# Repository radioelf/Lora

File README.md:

# Lora
Lora Radio
Molule E220 https://www.ebyte.com/en/product-view-news.html?id=1207

    Creative Commons License Disclaimer

  UNLESS OTHERWISE MUTUALLY AGREED TO BY THE PARTIES
  AND MAKES NO REPRESENTATIONS OR WARRANTIES OF ANY
  STATUTORY OR OTHERWISE, INCLUDING, WITHOUT LIMITAT
  FITNESS FOR A PARTICULAR PURPOSE, NONINFRINGEMENT,
  ACCURACY, OR THE PRESENCE OF ABSENCE OF ERRORS, WH
  DO NOT ALLOW THE EXCLUSION OF IMPLIED WARRANTIES,
  EXCEPT TO THE EXTENT REQUIRED BY APPLICABLE LAW, I
  ON ANY LEGAL THEORY FOR ANY SPECIAL, INCIDENTAL, C
  ARISING OUT OF THIS LICENSE OR THE USE OF THE WORK
  POSSIBILITY OF SUCH DAMAGES.

  http://creativecommons.org/licenses/by-sa/3.0/

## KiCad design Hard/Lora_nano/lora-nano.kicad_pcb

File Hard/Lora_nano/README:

PCB for Arduino Nano and module E220
Application: KiCad x86_64 on x86_64

Version: 7.0.0-rc1-unknown-00d77f624a~164~ubuntu22.04.1, release build

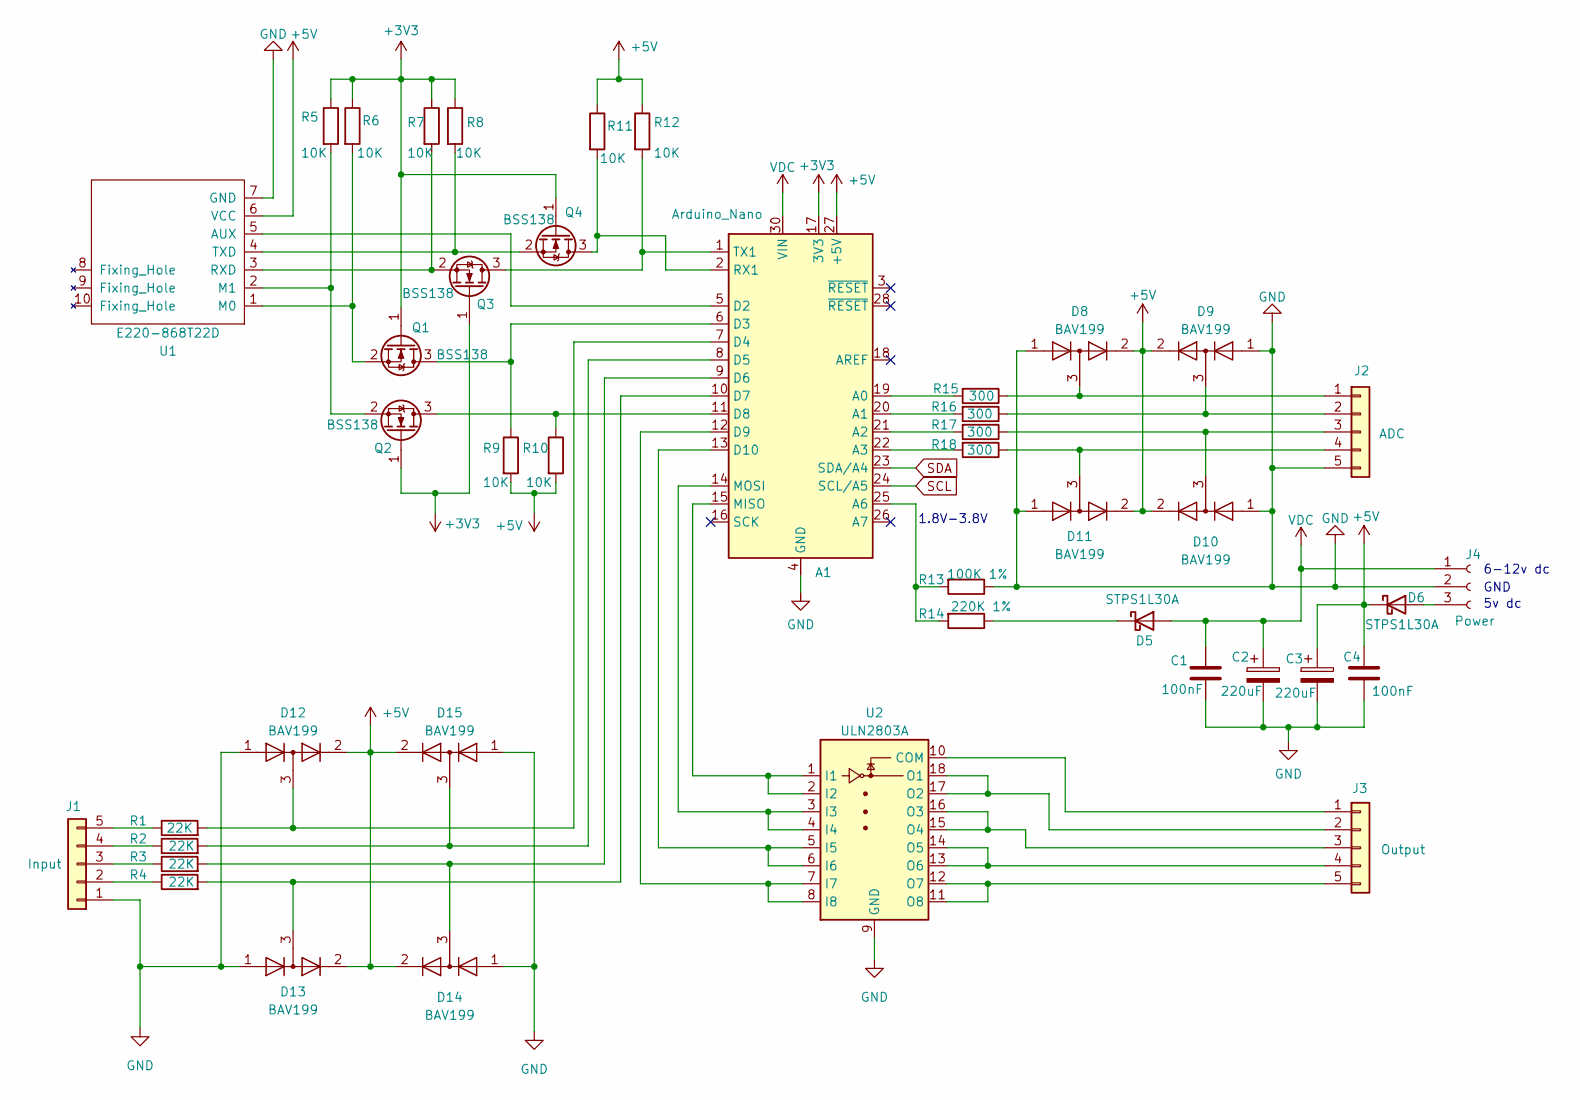
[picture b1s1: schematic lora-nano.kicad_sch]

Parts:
A1: Arduino_Nano
C1, C4: 100nF; C_0805_2012Metric
C2: 220uF; CP_Elec_8x6.2
C3: 220uF; CP_Elec_5x5.9
D5, D6: STPS1L30A; D_2010_5025Metric_Pad1.52x2.65mm_HandSolder
D8, D9, D10, D11, D12, D13, D14, D15: BAV199; SOT-23
J1: Input; PhoenixContact_MCV_1,5_5-G-3.5_1x05_P3.50mm_Vertical
J2: ADC; PhoenixContact_MCV_1,5_5-G-3.5_1x05_P3.50mm_Vertical
J3: Output; PhoenixContact_MCV_1,5_5-G-3.5_1x05_P3.50mm_Vertical
J4: Power; PhoenixContact_MCV_1,5_3-G-5.08_1x03_P5.08mm_Vertical
Q1, Q2, Q3, Q4: BSS138; SOT-23
R1, R2, R3, R4: 22K; R_0805_2012Metric
R5, R6, R7, R8, R9, R10, R11, R12: 10K; R_0805_2012Metric
R13: 100K 1%; R_Axial_DIN0204_L3.6mm_D1.6mm_P7.62mm_Horizontal
R14: 220K 1%; R_Axial_DIN0204_L3.6mm_D1.6mm_P7.62mm_Horizontal
R15, R16, R17, R18: 300; R_0805_2012Metric
U1: E220-868T22D; E32-xxxT20D-E220
U2: ULN2803A; SOIC-18W_7.5x11.6mm_P1.27mm

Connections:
+3V3: A1.17 (3V3), Q1.1 (G), Q2.1 (G), Q3.1 (G), Q4.1 (G), R5.1, R6.1, R7.1, R8.1
+5V: A1.27 (+5V), C3.1, C4.1, D6.1 (K), D8.2 (A), D9.2 (A), D10.2 (A), D11.2 (A), D12.2 (A), D13.2 (A), D14.2 (A), D15.2 (A), R9.2, R10.2, R11.1, R12.1, U1.6 (VCC); also elsewhere on the board
GND: A1.4 (GND), A1.29 (GND), C1.2, C2.2, C3.2, C4.2, D8.1 (K), D9.1 (K), D10.1 (K), D11.1 (K), D12.1 (K), D13.1 (K), D14.1 (K), D15.1 (K), J1.1, J2.5, J4.2, R13.1, U1.7 (GND), U2.9 (GND); also elsewhere on the board
unnamed: A1.19 (A0), R15.2
unnamed: A1.20 (A1), R16.2
unnamed: A1.21 (A2), R17.2
unnamed: A1.22 (A3), R18.2
unnamed: A1.25 (A6), R13.2, R14.2
unnamed: A1.5 (D2), U1.5 (AUX)
unnamed: A1.6 (D3), Q1.3 (D), R9.1
unnamed: A1.7 (D4), D12.3 (K), R1.2
unnamed: A1.8 (D5), D15.3 (K), R2.2
unnamed: A1.9 (D6), D14.3 (K), R3.2
unnamed: A1.10 (D7), D13.3 (K), R4.2
unnamed: A1.11 (D8), Q2.3 (D), R10.1
unnamed: A1.12 (D9), U2.7 (I7), U2.8 (I8)
unnamed: A1.13 (D10), U2.5 (I5), U2.6 (I6)
unnamed: A1.15 (MISO), U2.1 (I1), U2.2 (I2)
unnamed: A1.14 (MOSI), U2.3 (I3), U2.4 (I4)
unnamed 19: A1.2 (RX1), Q4.3 (D), R11.2; also elsewhere on the board
unnamed 20: A1.1 (TX1), Q3.3 (D), R12.2; also elsewhere on the board
unnamed: D5.1 (K), R14.1
unnamed: D6.2 (A), J4.3
unnamed: D8.3 (K), J2.1, R15.1
unnamed: D9.3 (K), J2.2, R16.1
unnamed: D10.3 (K), J2.3, R17.1
unnamed: D11.3 (K), J2.4, R18.1
unnamed: J1.2, R4.1
unnamed: J1.3, R3.1
unnamed: J1.4, R2.1
unnamed: J1.5, R1.1
unnamed: J3.1, U2.10 (COM)
unnamed: J3.2, U2.17 (O2), U2.18 (O1)
unnamed: J3.3, U2.15 (O4), U2.16 (O3)
unnamed: J3.4, U2.13 (O6), U2.14 (O5)
unnamed: J3.5, U2.11 (O8), U2.12 (O7)
unnamed: Q1.2 (S), R6.2, U1.1 (M0)
unnamed: Q2.2 (S), R5.2, U1.2 (M1)
unnamed: Q3.2 (S), R7.2, U1.3 (RXD)
unnamed: Q4.2 (S), R8.2, U1.4 (TXD)
SCL: A1.24 (SCL/A5); also elsewhere on the board
SDA: A1.23 (SDA/A4); also elsewhere on the board
VDC: A1.30 (VIN), C1.1, C2.1, D5.2 (A), J4.1

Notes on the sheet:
1.8V-3.8V
6-12v dc
5v dc
GND

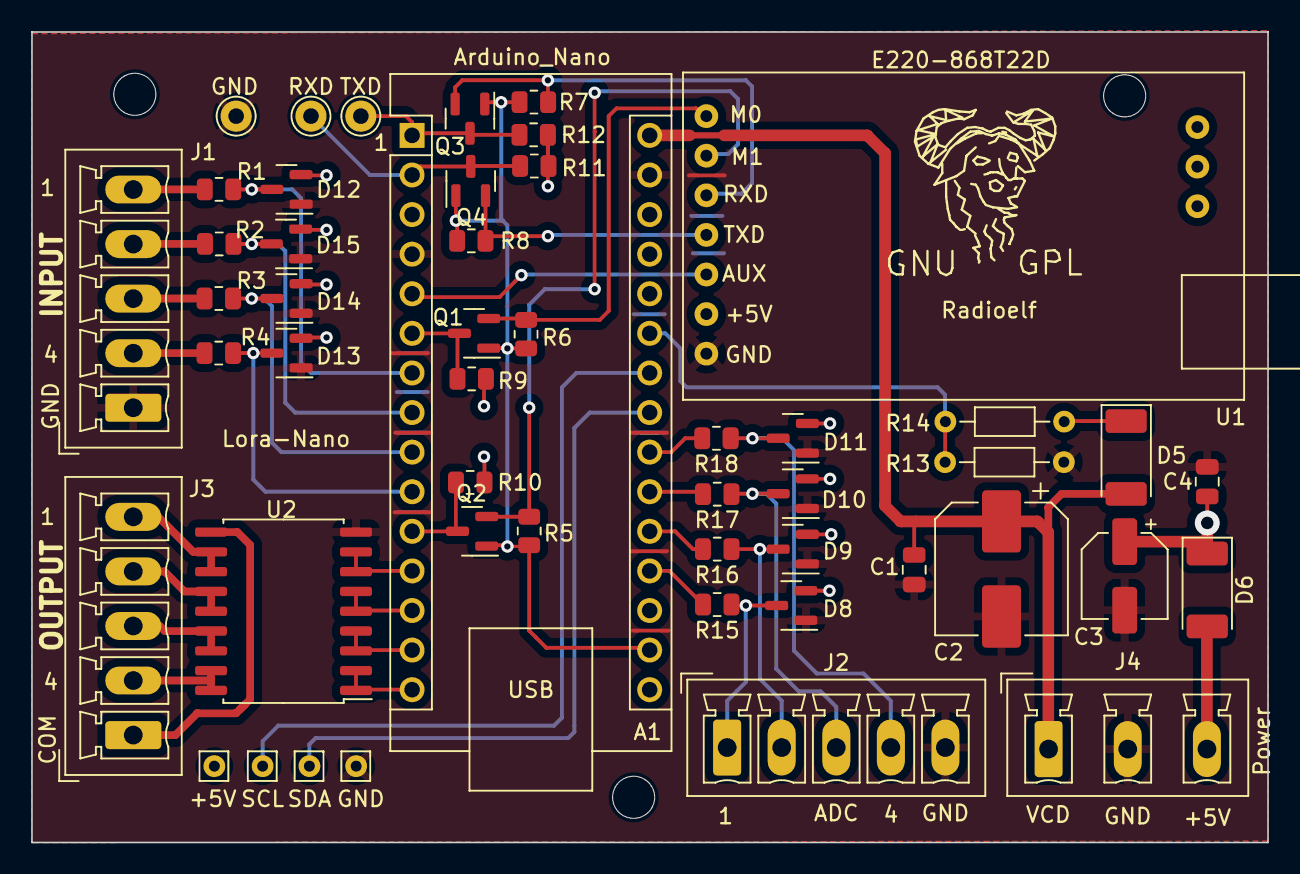
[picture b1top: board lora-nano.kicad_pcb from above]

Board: 2 copper layers, 79.3 x 52.0 mm, 50 parts (0 on the bottom side), 43 nets.

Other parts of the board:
+5V: Pin_D0.7mm_L6.5mm_W1.8mm_FlatFork
GND: Pin_D1.0mm_L10.0mm
GND#2: Pin_D0.7mm_L6.5mm_W1.8mm_FlatFork
RXD: Pin_D1.0mm_L10.0mm
SCL: Pin_D0.7mm_L6.5mm_W1.8mm_FlatFork
SDA: Pin_D0.7mm_L6.5mm_W1.8mm_FlatFork
TXD: Pin_D1.0mm_L10.0mm

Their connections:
+5V: +5V.1; also elsewhere on the board
GND: GND.1, GND#2.1; also elsewhere on the board
unnamed 19: RXD.1; also elsewhere on the board
unnamed 20: TXD.1; also elsewhere on the board
SCL: SCL.1; also elsewhere on the board
SDA: SDA.1; also elsewhere on the board

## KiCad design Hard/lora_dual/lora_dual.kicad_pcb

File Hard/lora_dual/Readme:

Dual PCB for E220 PIC12F675 and ESP12F 
Application: KiCad

Version: 6.99.0-unknown-492e6548ff~162~ubuntu22.04.1, release build

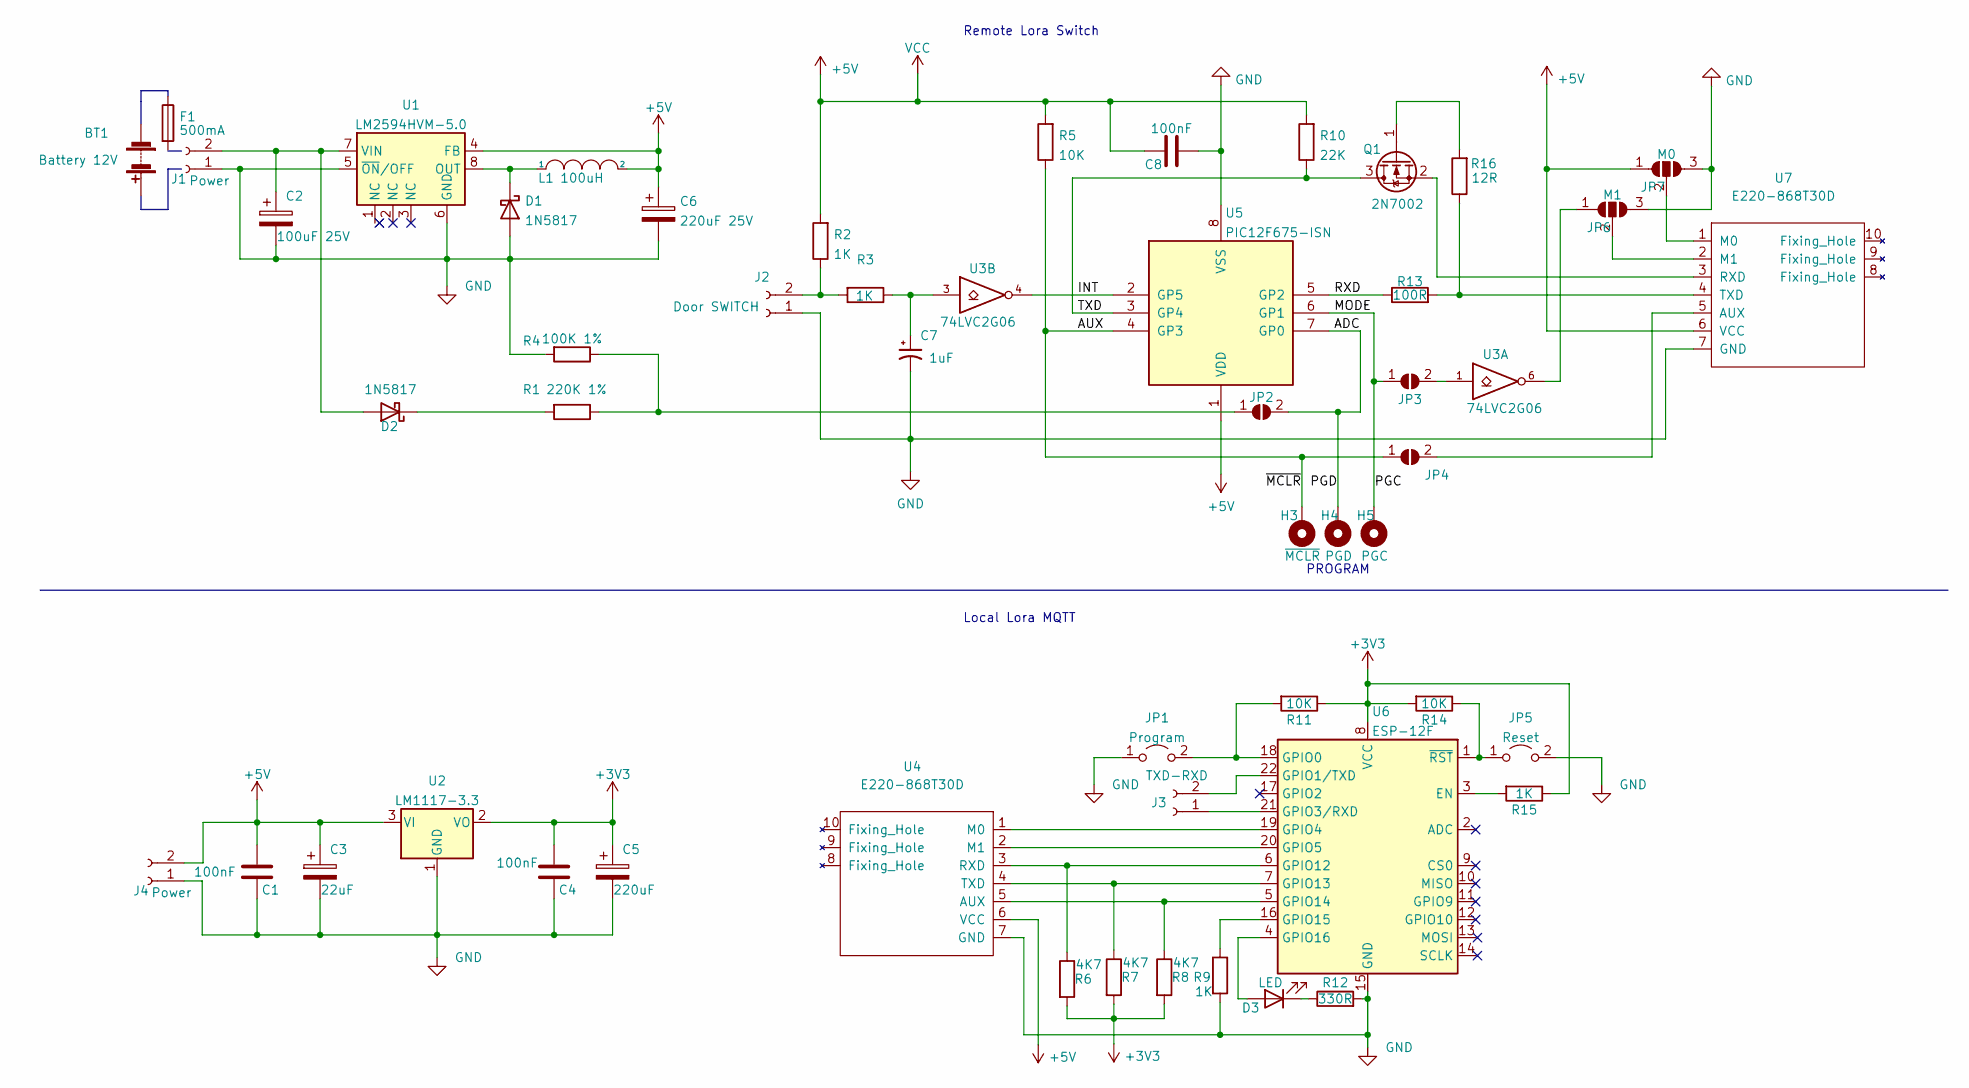
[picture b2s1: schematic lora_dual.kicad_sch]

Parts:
BT1: Battery 12V
C1, C4, C8: 100nF; C_0805_2012Metric
C2: 100uF 25V; CP_Elec_6.3x3
C3: 22uF; CP_Elec_4x5.8
C5: 220uF; CP_Elec_6.3x3
C6: 220uF 25V; CP_Elec_6.3x3
C7: 1uF; CP_Elec_3x5.3
D1, D2: 1N5817; D_DO-41_SOD81_P10.16mm_Horizontal
D3: LED; LED_0603_1608Metric
F1: 500mA
H3: ~{MCLR}; Pin_D0.7mm_L6.5mm_W1.8mm_FlatFork
H4: PGD; Pin_D0.7mm_L6.5mm_W1.8mm_FlatFork
H5: PGC; Pin_D0.7mm_L6.5mm_W1.8mm_FlatFork
J1, J4: Power; JWT_A3963_1x02_P3.96mm_Vertical
J2: Door SWITCH; JWT_A3963_1x02_P3.96mm_Vertical
J3: TXD-RXD; TestPoint_2Pads_Pitch2.54mm_Drill0.8mm
JP1: Program; TestPoint_2Pads_Pitch2.54mm_Drill0.8mm
JP2, JP4: Program; SolderJumper-2_P1.3mm_Open_RoundedPad1.0x1.5mm
JP3: PROGRAM; SolderJumper-2_P1.3mm_Open_RoundedPad1.0x1.5mm
JP5: Reset; TestPoint_2Pads_Pitch2.54mm_Drill0.8mm
JP6: M1; SolderJumper-3_P1.3mm_Open_RoundedPad1.0x1.5mm
JP7: M0; SolderJumper-3_P1.3mm_Open_RoundedPad1.0x1.5mm
L1: 100uH; L_Wuerth_WE-PDF
Q1: 2N7002; SOT-23
R1: 220K 1%; R_Axial_DIN0207_L6.3mm_D2.5mm_P10.16mm_Horizontal
R2, R3, R9, R15: 1K; R_0805_2012Metric
R4: 100K 1%; R_Axial_DIN0207_L6.3mm_D2.5mm_P10.16mm_Horizontal
R5, R11, R14: 10K; R_0805_2012Metric
R6, R7, R8: 4K7; R_0805_2012Metric
R10: 22K; R_0805_2012Metric
R12: 330R; R_0805_2012Metric
R13: 100R; R_0805_2012Metric
R16: 12R; R_0805_2012Metric
U1: LM2594HVM-5.0; SOIC-8_3.9x4.9mm_P1.27mm
U2: LM1117-3.3; SOT-223-3_TabPin2
U3: 74LVC2G06; SOT-23-6
U4, U7: E220-868T30D; E220-xxxTxxD
U5: PIC12F675-ISN; SOIC-8_3.9x4.9mm_P1.27mm
U6: ESP-12F; ESP-12E

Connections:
+3V3: C4.2, C5.1, R6.2, R7.2, R8.2, R11.1, R14.2, R15.1, U2.2 (VO), U6.8 (VCC)
+5V: C1.2, C3.1, C6.1, C8.1, J4.2, JP7.1 (A), L1.2, R2.2, R5.2, R10.2, U1.4 (FB), U2.3 (VI), U3.5 (VCC), U4.6 (VCC), U5.1 (VDD), U7.6 (VCC)
/ADC: H4.1, JP2.2 (B), U5.7 (GP0)
/AUX: H3.1, JP4.1 (A), R5.1, U5.4 (GP3)
/INT: U3.4, U5.2 (GP5)
/MODE: H5.1, JP3.1 (A), U5.6 (GP1)
/RXD: R13.1, U5.5 (GP2)
/TXD: Q1.3 (D), R10.1, U5.3 (GP4)
GND: C1.1, C2.2, C3.2, C4.1, C5.2, C6.2, C7.2, C8.2, D1.2 (A), J1.1, J2.1, J4.1, JP1.1 (A), JP5.2 (B), JP6.3 (B), JP7.3 (B), R4.2, R9.2, R12.2, U1.5 (~ON/OFF), U1.6 (GND), U2.1 (GND), U3.2 (GND), U4.7 (GND), U5.8 (VSS), U6.15 (GND), U7.7 (GND)
unnamed: C2.1, D2.2 (A), J1.2, U1.7 (VIN)
unnamed: C7.1, R3.1, U3.3
unnamed: D1.1 (K), L1.1, U1.8 (OUT)
unnamed: D2.1 (K), R1.2
unnamed: D3.1 (K), R12.1
unnamed: D3.2 (A), U6.4 (GPIO16)
unnamed: J2.2, R2.1, R3.2
unnamed: J3.1, U6.21 (GPIO3/RXD)
unnamed: J3.2, U6.22 (GPIO1/TXD)
unnamed: JP1.2 (B), R11.2, U6.18 (GPIO0)
unnamed: JP2.1 (A), R1.1, R4.1
unnamed: JP3.2 (B), U3.1
unnamed: JP4.2 (B), U7.5 (AUX)
unnamed: JP5.1 (A), R14.1, U6.1 (~RST)
unnamed: JP6.1 (A), U3.6
unnamed: JP6.2 (C), U7.2 (M1)
unnamed: JP7.2 (C), U7.1 (M0)
unnamed: Q1.1 (G), R16.2
unnamed: Q1.2 (S), U7.3 (RXD)
unnamed: R6.1, U4.3 (RXD), U6.6 (GPIO12)
unnamed: R7.1, U4.4 (TXD), U6.7 (GPIO13)
unnamed: R8.1, U4.5 (AUX), U6.5 (GPIO14)
unnamed: R9.1, U6.16 (GPIO15)
unnamed: R13.2, R16.1, U7.4 (TXD)
unnamed: R15.2, U6.3 (EN)
unnamed: U4.1 (M0), U6.19 (GPIO4)
unnamed: U4.2 (M1), U6.20 (GPIO5)

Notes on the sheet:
Local Lora MQTT
PROGRAM
Remote Lora Switch

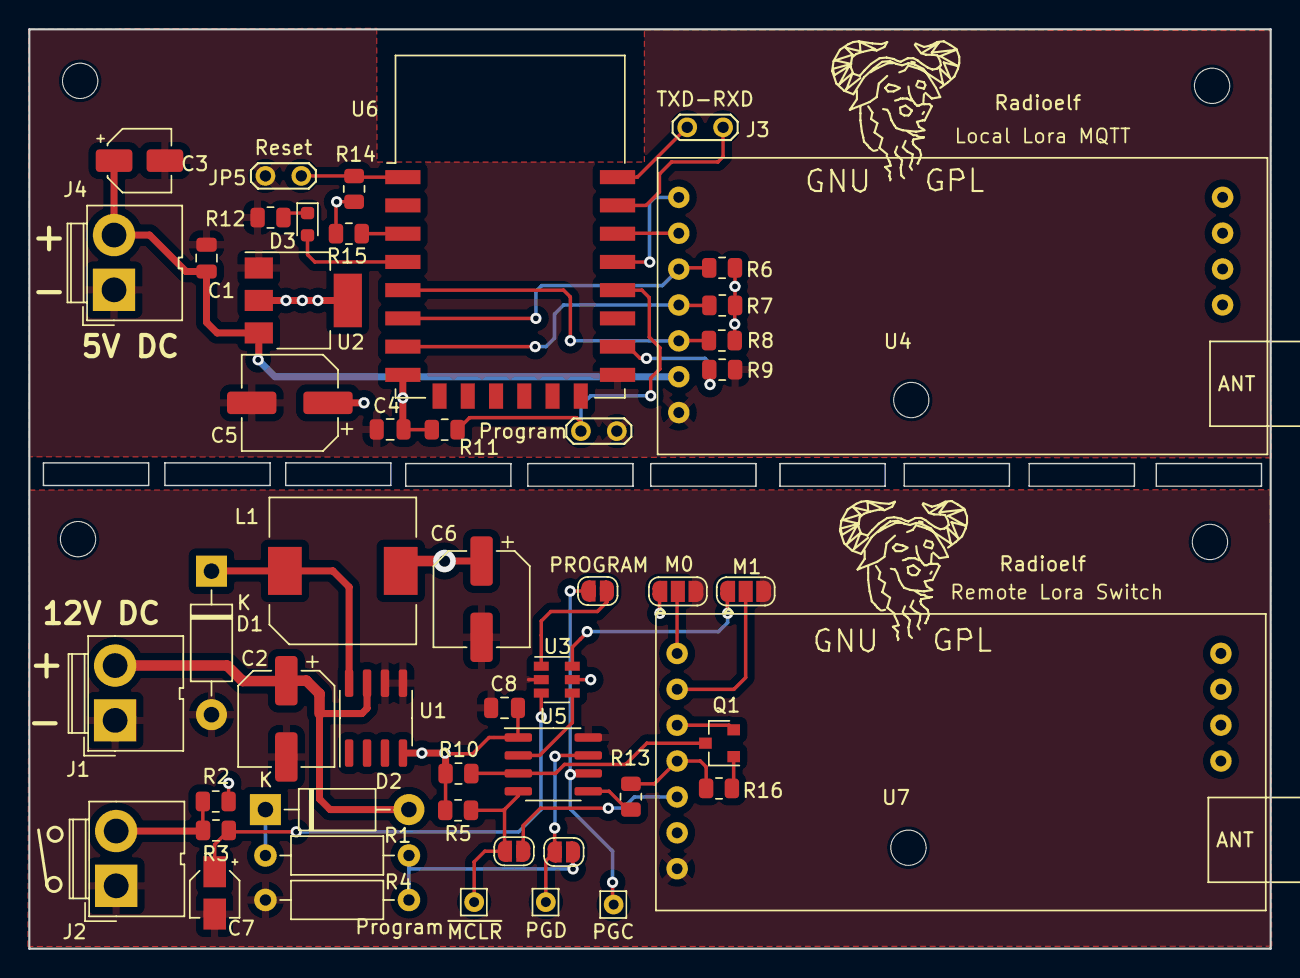
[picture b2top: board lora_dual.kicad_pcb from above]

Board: 2 copper layers, 87.9 x 65.1 mm, 52 parts (0 on the bottom side), 36 nets.

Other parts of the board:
Radioelf: Symbol_GNU-Logo_SilkscreenTop
Radioelf#2: Symbol_GNU-Logo_SilkscreenTop

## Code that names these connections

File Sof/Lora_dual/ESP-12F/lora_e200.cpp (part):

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
#include "ESP8266_OTA.h"

// ESP8266 RX GPIO13<-- TX E220, ESP8266 TX GPIO12--> RX E220, M0 ->GPIO4, M1 ->GPIO5, AUX->GPIO14
// pin led estado (gpio16)
#define LedPin 16

// Configuración red WiFi
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
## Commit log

2022-12-11 Create Lora_nano
2023-01-15 Create Gerber\
2023-01-15 Create \Gerber
2023-01-27 Create serial_lora.py
    Para usar con Appdaemon
2023-01-28 Create sensor.yaml
    Para crear entidades de sensores en Home Assistant
2023-01-28 Create switch.yaml
    Para crear entidades de interruptores en Home Assistant
